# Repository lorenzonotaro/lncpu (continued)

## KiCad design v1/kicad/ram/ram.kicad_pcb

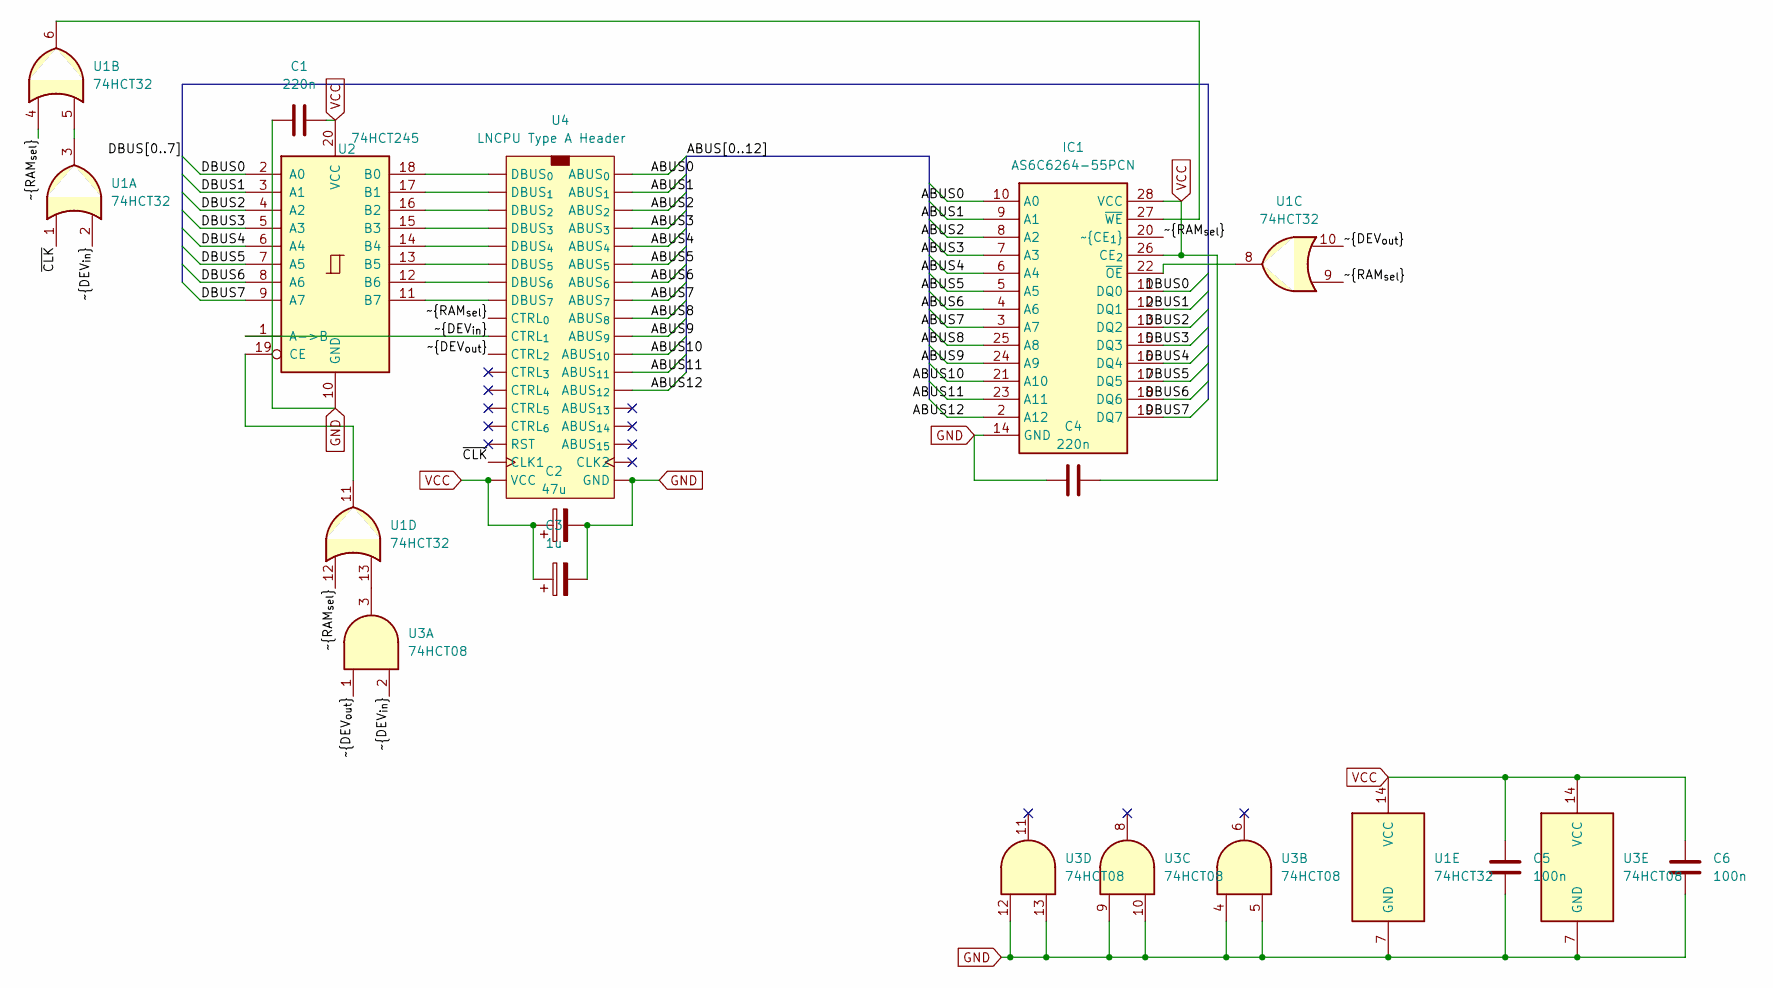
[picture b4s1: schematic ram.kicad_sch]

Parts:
C1, C4: 220n; C_Disc_D5.0mm_W2.5mm_P2.50mm
C2: 47u; CP_Radial_D5.0mm_P2.50mm
C3: 1u; CP_Radial_D4.0mm_P2.00mm-Large-Holes
C5, C6: 100n; C_Disc_D5.0mm_W2.5mm_P2.50mm
IC1: AS6C6264-55PCN; DIP1524W51P254L3632H394Q28N; Mouser Part Number 913-AS6C6264-55PCN
U1: 74HCT32; DIP-14_W7.62mm_LongPads
U2: 74HCT245; DIP-20_W7.62mm_LongPads
U3: 74HCT08; DIP-14_W7.62mm_LongPads
U4: LNCPU Type A Header; LNCPU_Type_A_Header

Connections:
/ABUS0: IC1.10 (A0), U4.4 (ABUS_{0})
/ABUS1: IC1.9 (A1), U4.6 (ABUS_{1})
/ABUS2: IC1.8 (A2), U4.8 (ABUS_{2})
/ABUS3: IC1.7 (A3), U4.10 (ABUS_{3})
/ABUS4: IC1.6 (A4), U4.12 (ABUS_{4})
/ABUS5: IC1.5 (A5), U4.14 (ABUS_{5})
/ABUS6: IC1.4 (A6), U4.16 (ABUS_{6})
/ABUS7: IC1.3 (A7), U4.18 (ABUS_{7})
/ABUS8: IC1.25 (A8), U4.20 (ABUS_{8})
/ABUS9: IC1.24 (A9), U4.22 (ABUS_{9})
/ABUS10: IC1.21 (A10), U4.24 (ABUS_{10})
/ABUS11: IC1.23 (A11), U4.26 (ABUS_{11})
/ABUS12: IC1.2 (A12), U4.28 (ABUS_{12})
/DBUS0: IC1.11 (DQ0), U2.2 (A0)
/DBUS1: IC1.12 (DQ1), U2.3 (A1)
/DBUS2: IC1.13 (DQ2), U2.4 (A2)
/DBUS3: IC1.15 (DQ3), U2.5 (A3)
/DBUS4: IC1.16 (DQ4), U2.6 (A4)
/DBUS5: IC1.17 (DQ5), U2.7 (A5)
/DBUS6: IC1.18 (DQ6), U2.8 (A6)
/DBUS7: IC1.19 (DQ7), U2.9 (A7)
/~CLK: U1.1, U4.35 (CLK1)
/~DEV_{in}: U1.2, U2.1 (A->B), U3.2, U4.5 (CTRL_{1})
/~DEV_{out}: U1.10, U3.1, U4.7 (CTRL_{2})
/~RAM_{sel}: IC1.20 (~CE_{1}), U1.4, U1.9, U1.12, U4.3 (CTRL_{0})
GND: C1.1, C2.2, C3.2, C4.1, C5.1, C6.1, IC1.14 (GND), U1.7 (GND), U2.10 (GND), U3.4, U3.5, U3.7 (GND), U3.9, U3.10, U3.12, U3.13, U4.1 (GND), U4.37 (GND), U4.38 (GND), U4.39 (GND)
unnamed: IC1.22 (~OE), U1.8
unnamed: IC1.27 (~WE), U1.6
unnamed: U1.3, U1.5
unnamed: U1.13, U3.3
unnamed: U2.18 (B0), U4.19 (DBUS_{0})
unnamed: U2.17 (B1), U4.21 (DBUS_{1})
unnamed: U2.16 (B2), U4.23 (DBUS_{2})
unnamed: U2.15 (B3), U4.25 (DBUS_{3})
unnamed: U2.14 (B4), U4.27 (DBUS_{4})
unnamed: U2.13 (B5), U4.29 (DBUS_{5})
unnamed: U2.12 (B6), U4.31 (DBUS_{6})
unnamed: U2.11 (B7), U4.33 (DBUS_{7})
unnamed: U1.11, U2.19 (CE)
VCC: C1.2, C2.1, C3.1, C4.2, C5.2, C6.2, IC1.26 (CE_{2}), IC1.28 (VCC), U1.14 (VCC), U2.20 (VCC), U3.14 (VCC), U4.2 (VCC), U4.40 (VCC)

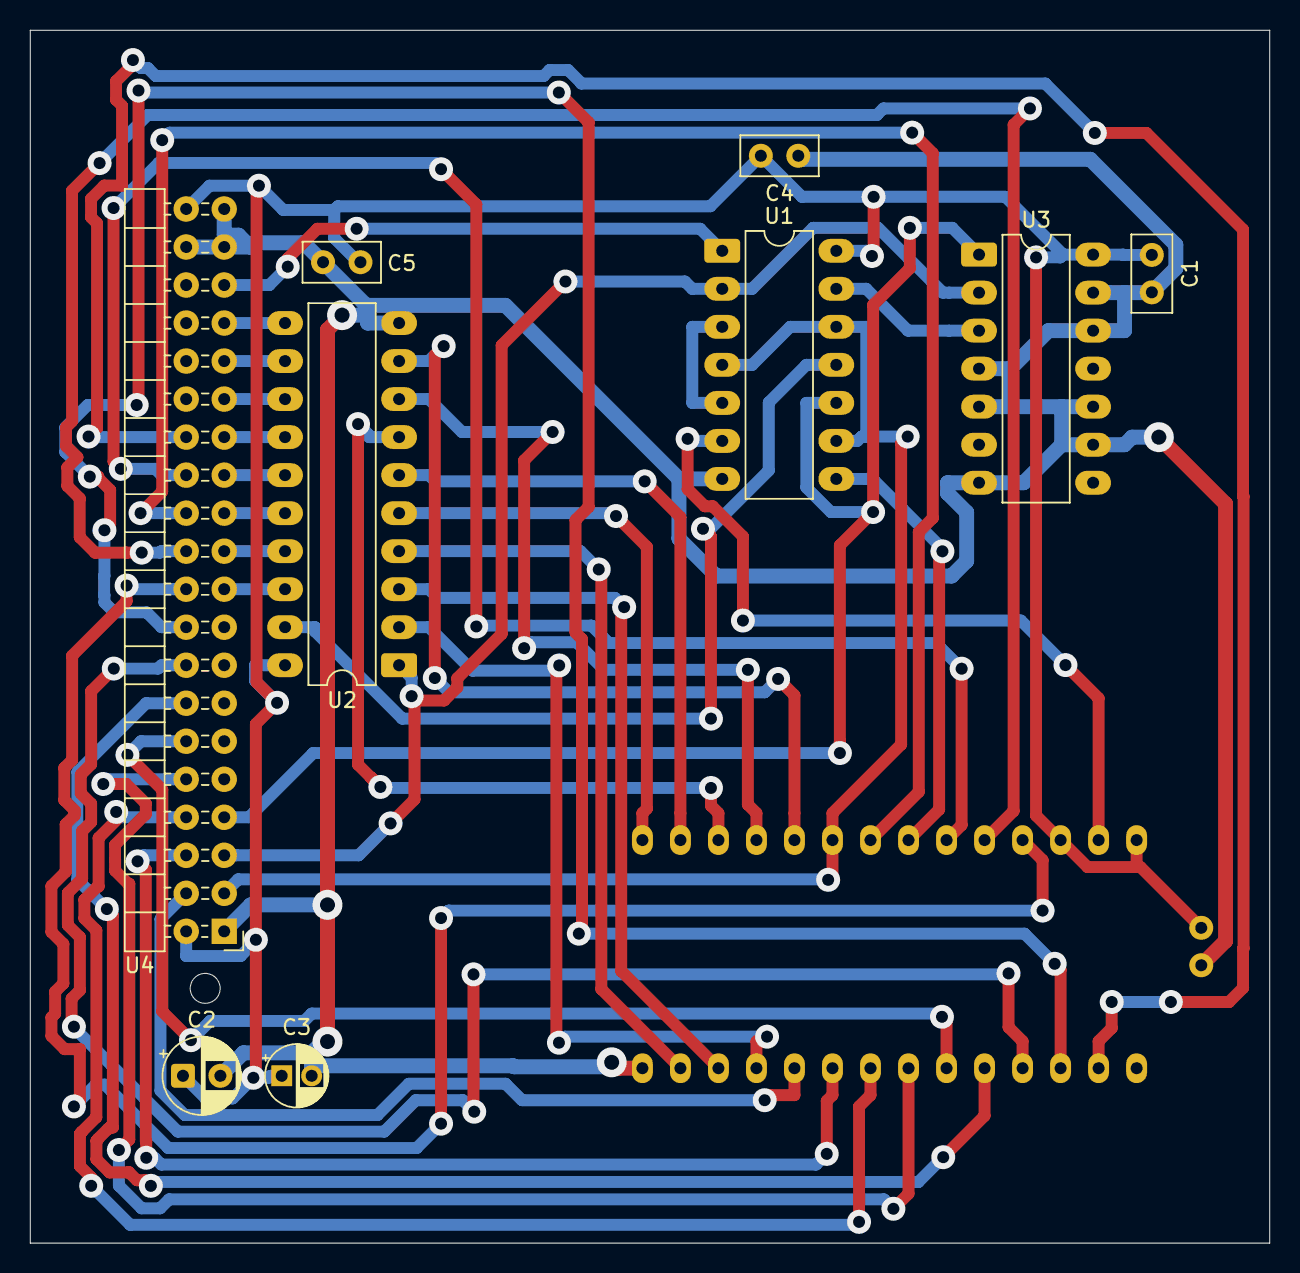
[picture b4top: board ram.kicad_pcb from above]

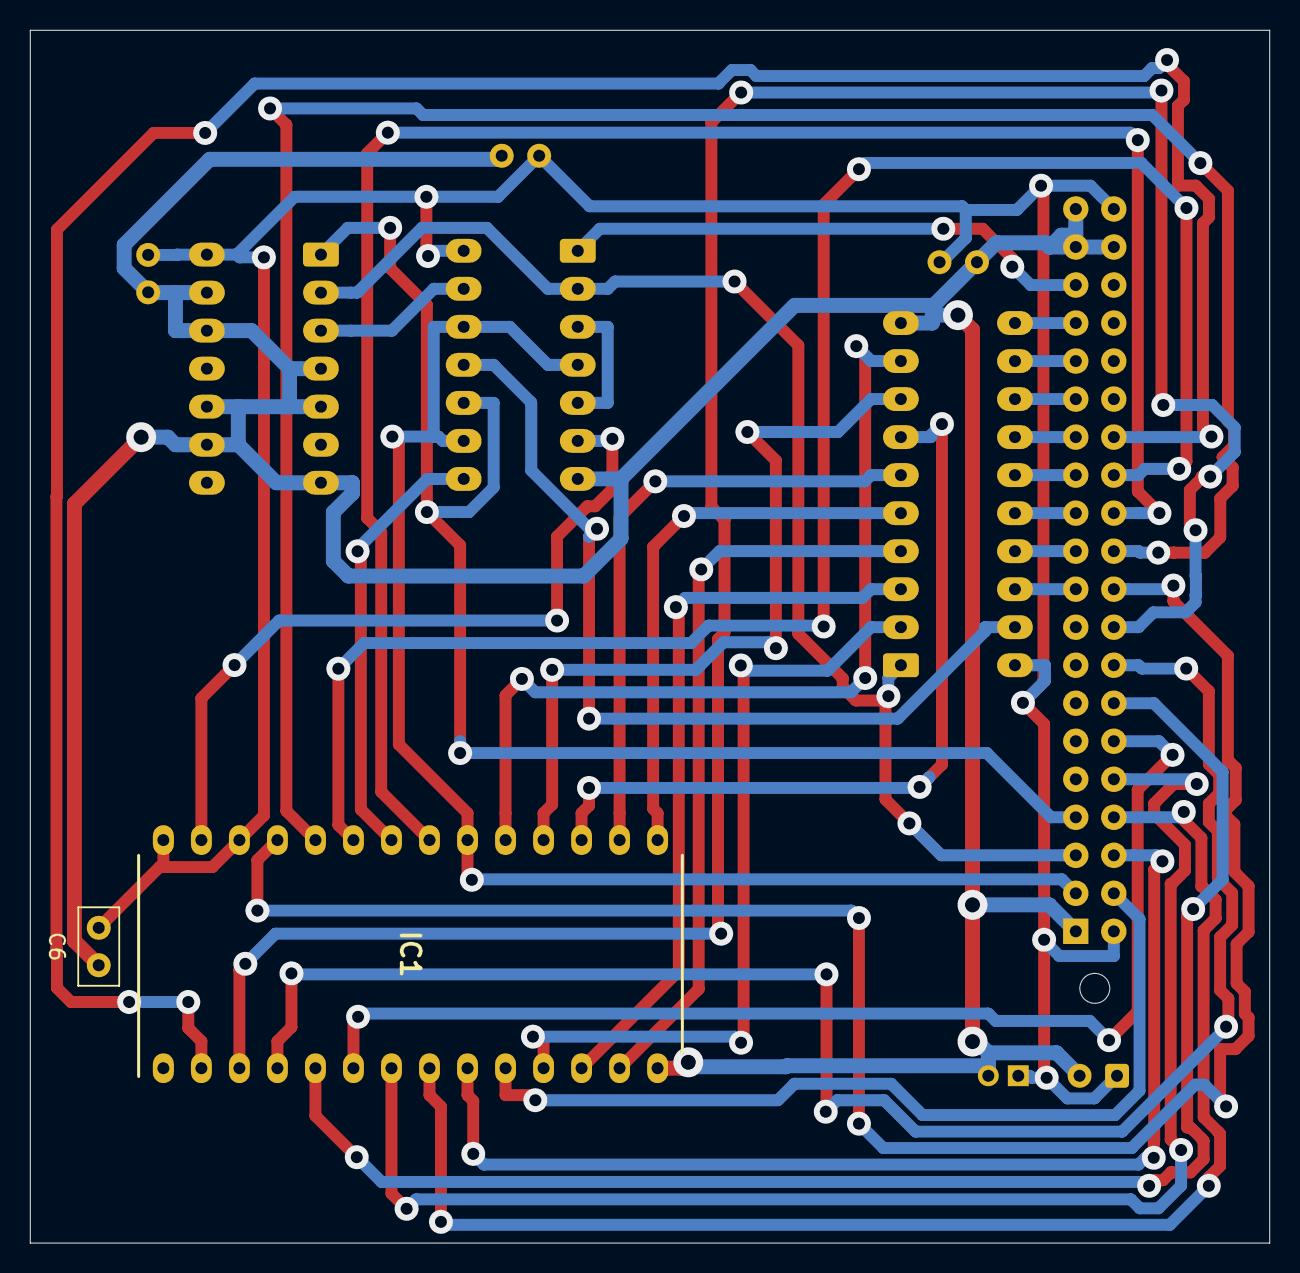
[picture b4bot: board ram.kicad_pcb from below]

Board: 2 copper layers, 82.8 x 81.0 mm, 11 parts (2 on the bottom side), 40 nets.

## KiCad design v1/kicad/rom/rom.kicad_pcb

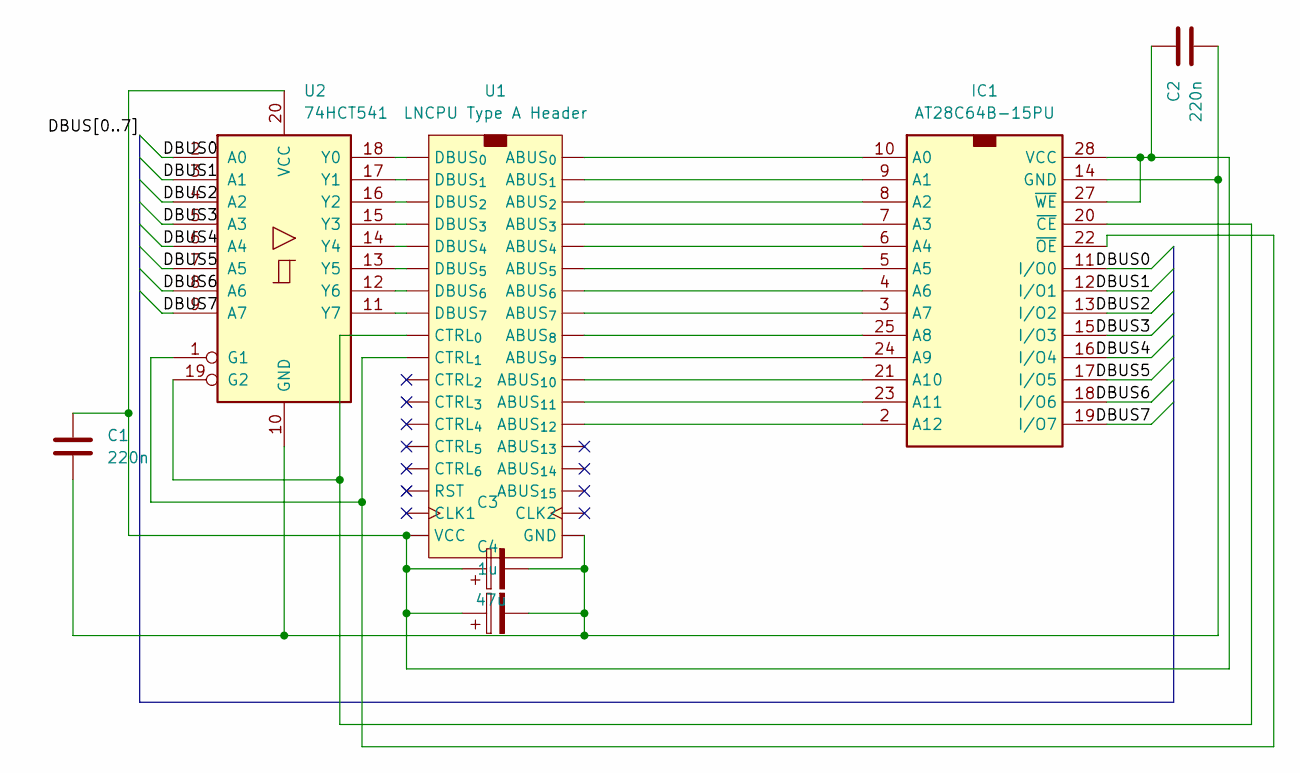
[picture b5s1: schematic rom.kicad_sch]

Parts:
C1, C2: 220n; C_Disc_D5.0mm_W2.5mm_P2.50mm
C3: 47u; CP_Radial_D5.0mm_P2.00mm
C4: 1u; CP_Radial_D4.0mm_P2.00mm-Large-Holes
IC1: AT28C64B-15PU; DIP1556W56P254L3702H483Q28N; Manufacturer_Part_Number AT28C64B-15PU; Mouser Part Number 556-AT28C64B15PU
U1: LNCPU Type A Header; LNCPU_Type_A_Header
U2: 74HCT541; DIP-20_W7.62mm_LongPads

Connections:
/DBUS0: IC1.11 (I/O0), U2.2 (A0)
/DBUS1: IC1.12 (I/O1), U2.3 (A1)
/DBUS2: IC1.13 (I/O2), U2.4 (A2)
/DBUS3: IC1.15 (I/O3), U2.5 (A3)
/DBUS4: IC1.16 (I/O4), U2.6 (A4)
/DBUS5: IC1.17 (I/O5), U2.7 (A5)
/DBUS6: IC1.18 (I/O6), U2.8 (A6)
/DBUS7: IC1.19 (I/O7), U2.9 (A7)
unnamed: IC1.10 (A0), U1.4 (ABUS_{0})
unnamed: IC1.9 (A1), U1.6 (ABUS_{1})
unnamed: IC1.8 (A2), U1.8 (ABUS_{2})
unnamed: IC1.7 (A3), U1.10 (ABUS_{3})
unnamed: IC1.6 (A4), U1.12 (ABUS_{4})
unnamed: IC1.5 (A5), U1.14 (ABUS_{5})
unnamed: IC1.4 (A6), U1.16 (ABUS_{6})
unnamed: IC1.3 (A7), U1.18 (ABUS_{7})
unnamed: IC1.25 (A8), U1.20 (ABUS_{8})
unnamed: IC1.24 (A9), U1.22 (ABUS_{9})
unnamed: IC1.21 (A10), U1.24 (ABUS_{10})
unnamed: IC1.23 (A11), U1.26 (ABUS_{11})
unnamed: IC1.2 (A12), U1.28 (ABUS_{12})
unnamed: C1.2, C2.2, C3.2, C4.2, IC1.14 (GND), U1.1 (GND), U1.37 (GND), U1.38 (GND), U1.39 (GND), U2.10 (GND)
unnamed: C1.1, C2.1, C3.1, C4.1, IC1.27 (~WE), IC1.28 (VCC), U1.2 (VCC), U1.40 (VCC), U2.20 (VCC)
unnamed: IC1.20 (~CE), U1.3 (CTRL_{0}), U2.19 (G2)
unnamed: IC1.22 (~OE), U1.5 (CTRL_{1}), U2.1 (G1)
unnamed: U1.19 (DBUS_{0}), U2.18 (Y0)
unnamed: U1.21 (DBUS_{1}), U2.17 (Y1)
unnamed: U1.23 (DBUS_{2}), U2.16 (Y2)
unnamed: U1.25 (DBUS_{3}), U2.15 (Y3)
unnamed: U1.27 (DBUS_{4}), U2.14 (Y4)
unnamed: U1.29 (DBUS_{5}), U2.13 (Y5)
unnamed: U1.31 (DBUS_{6}), U2.12 (Y6)
unnamed: U1.33 (DBUS_{7}), U2.11 (Y7)

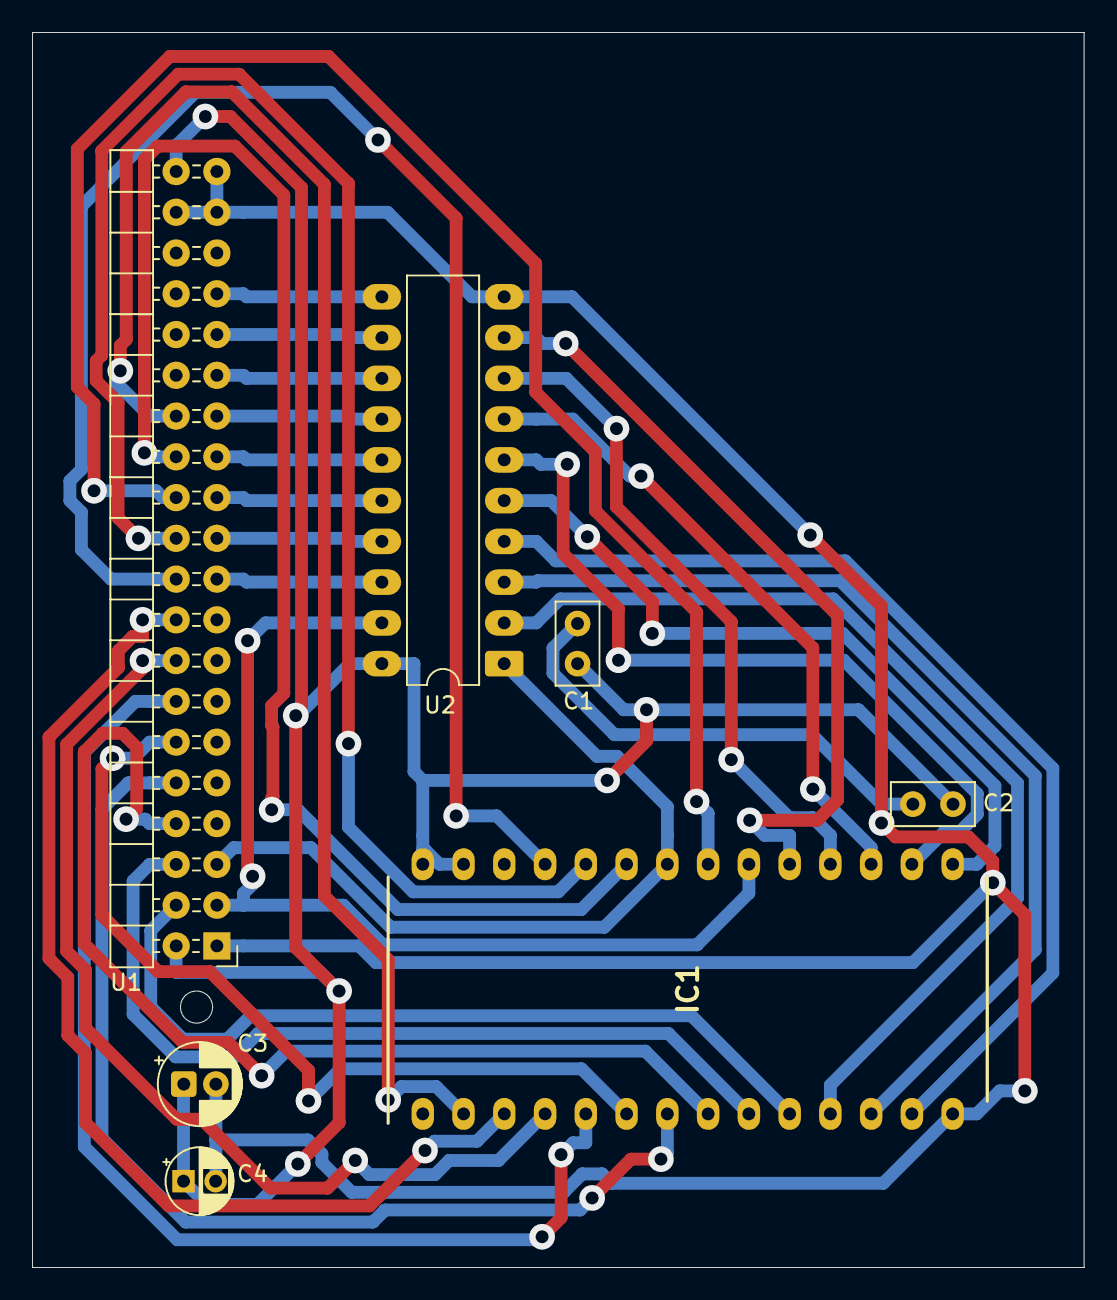
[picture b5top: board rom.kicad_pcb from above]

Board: 2 copper layers, 65.5 x 77.0 mm, 7 parts (0 on the bottom side), 33 nets.

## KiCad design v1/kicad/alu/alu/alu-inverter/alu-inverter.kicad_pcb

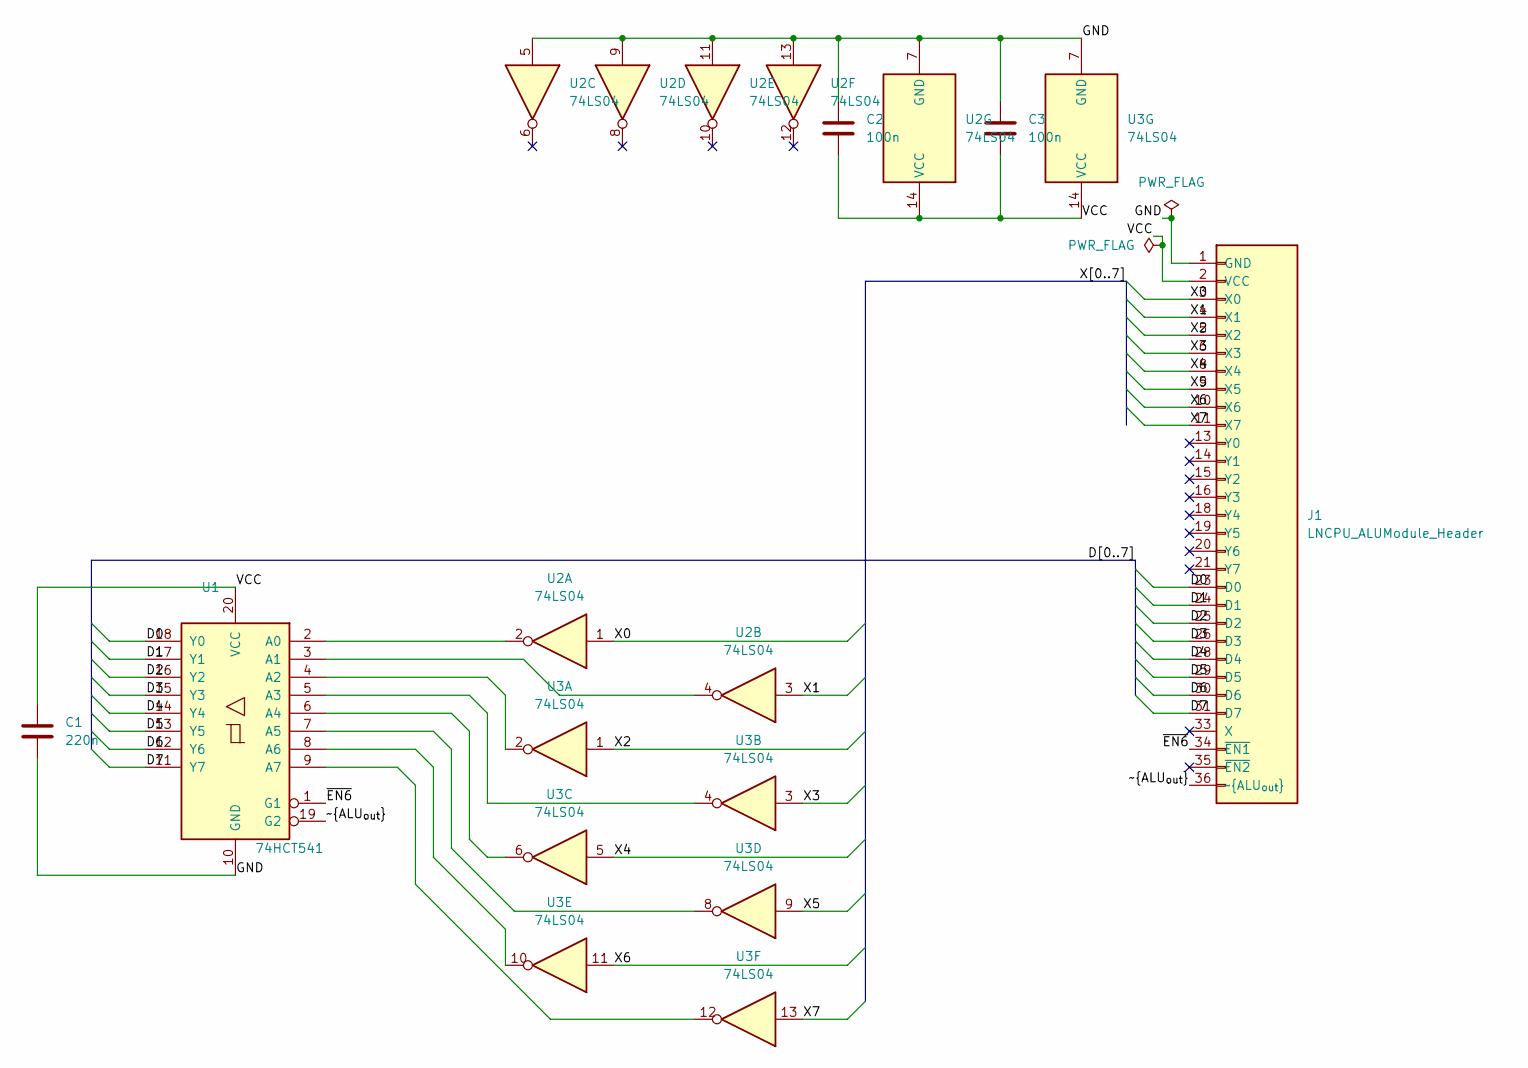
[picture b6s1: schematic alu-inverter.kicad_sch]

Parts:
C1: 220n; C_Disc_D5.0mm_W2.5mm_P5.00mm
C2, C3: 100n; C_Disc_D5.0mm_W2.5mm_P5.00mm
J1: LNCPU_ALUModule_Header; LNCPU_ALU_Module_Header
U1: 74HCT541; DIP-20_W7.62mm_LongPads
U2, U3: 74LS04; DIP-14_W7.62mm_LongPads

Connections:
/D0: J1.23 (D0), U1.18 (Y0)
/D1: J1.24 (D1), U1.17 (Y1)
/D2: J1.25 (D2), U1.16 (Y2)
/D3: J1.26 (D3), U1.15 (Y3)
/D4: J1.28 (D4), U1.14 (Y4)
/D5: J1.29 (D5), U1.13 (Y5)
/D6: J1.30 (D6), U1.12 (Y6)
/D7: J1.31 (D7), U1.11 (Y7)
/GND: C1.2, C2.1, C3.1, J1.1 (GND), J1.7 (GND), J1.12 (GND), J1.17 (GND), J1.22 (GND), J1.27 (GND), J1.32 (GND), J1.37 (GND), U1.10 (GND), U2.5, U2.7 (GND), U2.9, U2.11, U2.13, U3.7 (GND)
/VCC: C1.1, C2.2, C3.2, J1.2 (VCC), J1.38 (VCC), U1.20 (VCC), U2.14 (VCC), U3.14 (VCC)
/X0: J1.3 (X0), U2.1
/X1: J1.4 (X1), U2.3
/X2: J1.5 (X2), U3.1
/X3: J1.6 (X3), U3.3
/X4: J1.8 (X4), U3.5
/X5: J1.9 (X5), U3.9
/X6: J1.10 (X6), U3.11
/X7: J1.11 (X7), U3.13
/~ALU_{out}: J1.36 (~ALU_{out}), U1.19 (G2)
/~EN6: J1.34 (~EN1), U1.1 (G1)
unnamed: U1.2 (A0), U2.2
unnamed: U1.3 (A1), U2.4
unnamed: U1.4 (A2), U3.2
unnamed: U1.5 (A3), U3.4
unnamed: U1.6 (A4), U3.6
unnamed: U1.7 (A5), U3.8
unnamed: U1.8 (A6), U3.10
unnamed: U1.9 (A7), U3.12

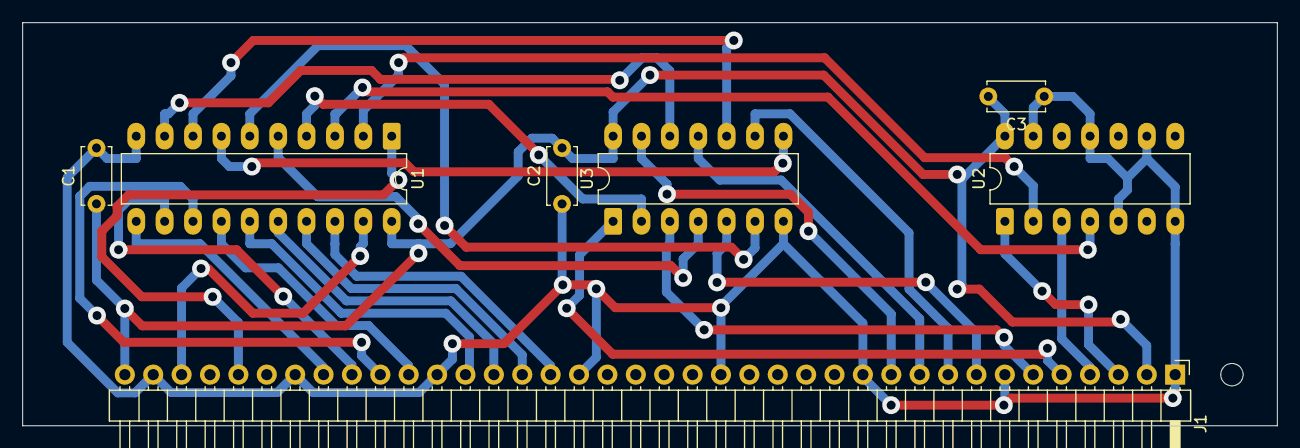
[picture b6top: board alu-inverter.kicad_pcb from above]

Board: 2 copper layers, 112.3 x 36.1 mm, 7 parts (0 on the bottom side), 28 nets.

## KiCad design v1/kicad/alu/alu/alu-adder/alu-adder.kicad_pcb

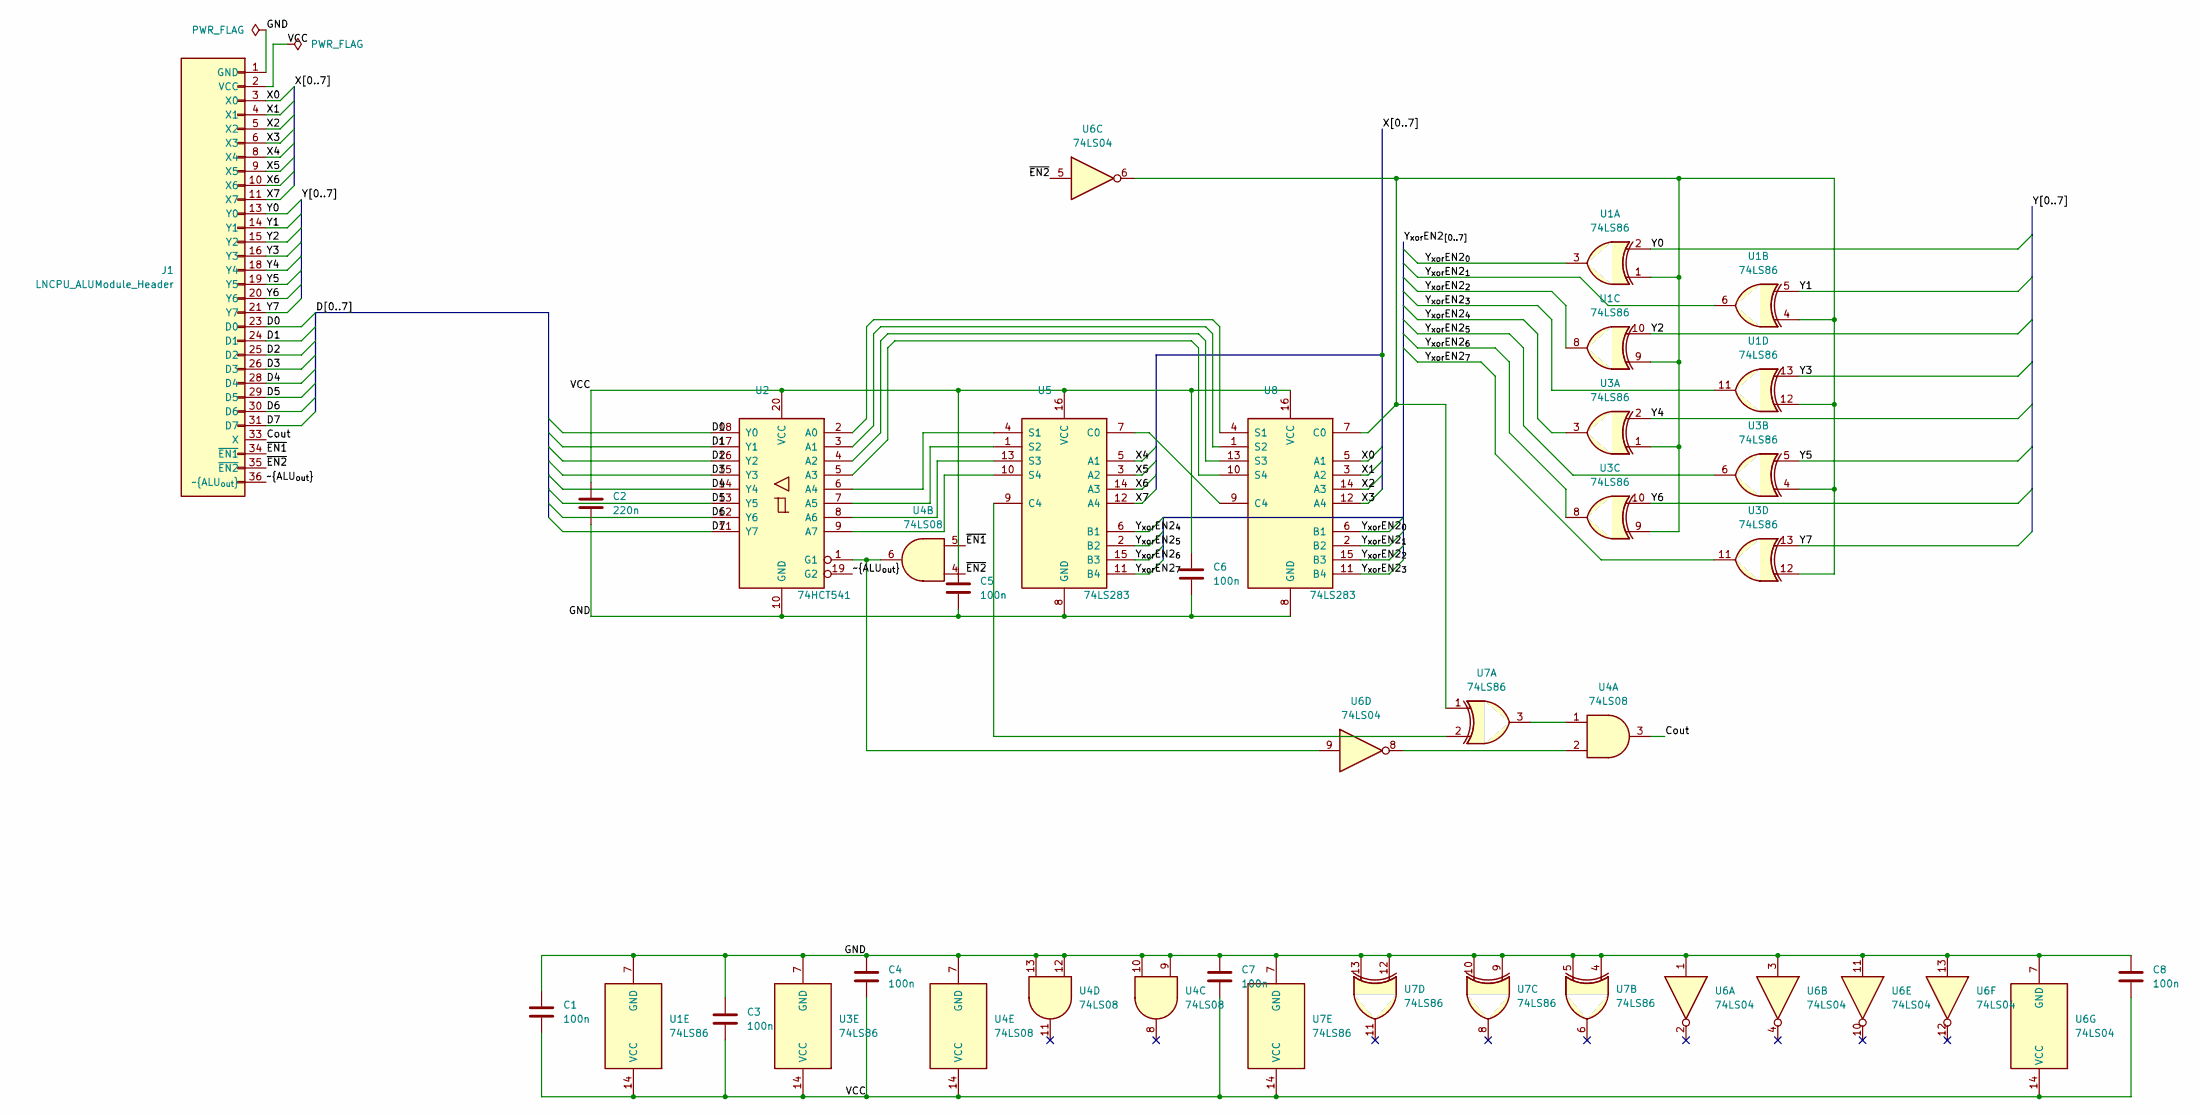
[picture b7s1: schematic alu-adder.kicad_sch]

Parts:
C1, C3, C4, C5, C6, C7, C8: 100n; C_Disc_D5.0mm_W2.5mm_P5.00mm
C2: 220n; C_Disc_D5.0mm_W2.5mm_P5.00mm
J1: LNCPU_ALUModule_Header; LNCPU_ALU_Module_Header
U1, U3, U7: 74LS86; DIP-14_W7.62mm_LongPads
U2: 74HCT541; DIP-20_W7.62mm_LongPads
U4: 74LS08; DIP-14_W7.62mm_LongPads
U5, U8: 74LS283; DIP-16_W7.62mm_LongPads
U6: 74LS04; DIP-14_W7.62mm_LongPads

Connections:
/Cout: J1.33 (X), U4.3
/D0: J1.23 (D0), U2.18 (Y0)
/D1: J1.24 (D1), U2.17 (Y1)
/D2: J1.25 (D2), U2.16 (Y2)
/D3: J1.26 (D3), U2.15 (Y3)
/D4: J1.28 (D4), U2.14 (Y4)
/D5: J1.29 (D5), U2.13 (Y5)
/D6: J1.30 (D6), U2.12 (Y6)
/D7: J1.31 (D7), U2.11 (Y7)
/GND: C1.1, C2.2, C3.1, C4.1, C5.2, C6.2, C7.1, C8.1, J1.1 (GND), J1.7 (GND), J1.12 (GND), J1.17 (GND), J1.22 (GND), J1.27 (GND), J1.32 (GND), J1.37 (GND), U1.7 (GND), U2.10 (GND), U3.7 (GND), U4.7 (GND), U4.9, U4.10, U4.12, U4.13, U5.8 (GND), U6.1, U6.3, U6.7 (GND), U6.11, U6.13, U7.4, U7.5, U7.7 (GND), U7.9, U7.10, U7.12, U7.13, U8.8 (GND)
/VCC: C1.2, C2.1, C3.2, C4.2, C5.1, C6.1, C7.2, C8.2, J1.2 (VCC), J1.38 (VCC), U1.14 (VCC), U2.20 (VCC), U3.14 (VCC), U4.14 (VCC), U5.16 (VCC), U6.14 (VCC), U7.14 (VCC), U8.16 (VCC)
/X0: J1.3 (X0), U8.5 (A1)
/X1: J1.4 (X1), U8.3 (A2)
/X2: J1.5 (X2), U8.14 (A3)
/X3: J1.6 (X3), U8.12 (A4)
/X4: J1.8 (X4), U5.5 (A1)
/X5: J1.9 (X5), U5.3 (A2)
/X6: J1.10 (X6), U5.14 (A3)
/X7: J1.11 (X7), U5.12 (A4)
/Y0: J1.13 (Y0), U1.2
/Y1: J1.14 (Y1), U1.5
/Y2: J1.15 (Y2), U1.10
/Y3: J1.16 (Y3), U1.13
/Y4: J1.18 (Y4), U3.2
/Y5: J1.19 (Y5), U3.5
/Y6: J1.20 (Y6), U3.10
/Y7: J1.21 (Y7), U3.13
/Y_{xor}EN2_{0}: U1.3, U8.6 (B1)
/Y_{xor}EN2_{1}: U1.6, U8.2 (B2)
/Y_{xor}EN2_{2}: U1.8, U8.15 (B3)
/Y_{xor}EN2_{3}: U1.11, U8.11 (B4)
/Y_{xor}EN2_{4}: U3.3, U5.6 (B1)
/Y_{xor}EN2_{5}: U3.6, U5.2 (B2)
/Y_{xor}EN2_{6}: U3.8, U5.15 (B3)
/Y_{xor}EN2_{7}: U3.11, U5.11 (B4)
/~ALU_{out}: J1.36 (~ALU_{out}), U2.19 (G2)
/~EN1: J1.34 (~EN1), U4.5
/~EN2: J1.35 (~EN2), U4.4, U6.5
unnamed: U2.2 (A0), U8.4 (S1)
unnamed: U2.3 (A1), U8.1 (S2)
unnamed: U2.4 (A2), U8.13 (S3)
unnamed: U2.5 (A3), U8.10 (S4)
unnamed: U2.6 (A4), U5.4 (S1)
unnamed: U2.7 (A5), U5.1 (S2)
unnamed: U2.8 (A6), U5.13 (S3)
unnamed: U2.9 (A7), U5.10 (S4)
unnamed: U2.1 (G1), U4.6, U6.9
unnamed: U4.1, U7.3
unnamed: U4.2, U6.8
unnamed: U5.7 (C0), U8.9 (C4)
unnamed: U5.9 (C4), U7.2
unnamed: U1.1, U1.4, U1.9, U1.12, U3.1, U3.4, U3.9, U3.12, U6.6, U7.1, U8.7 (C0)

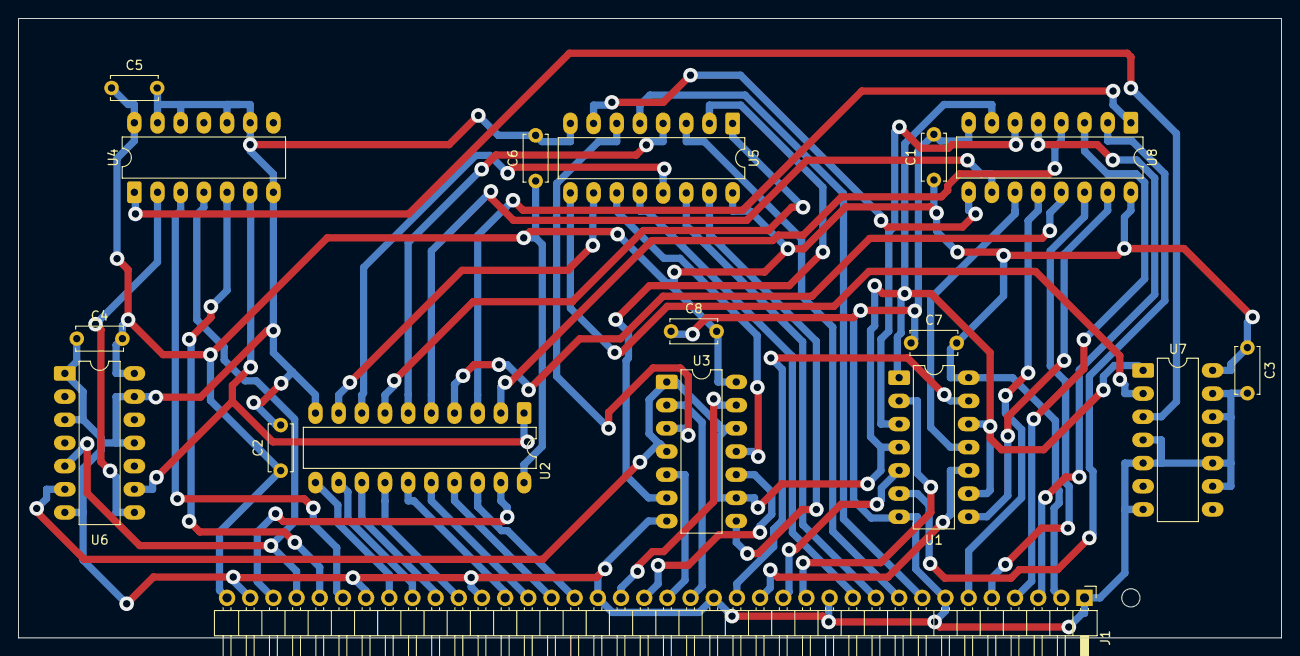
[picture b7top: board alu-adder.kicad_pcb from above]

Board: 2 copper layers, 138.4 x 67.9 mm, 17 parts (0 on the bottom side), 52 nets.

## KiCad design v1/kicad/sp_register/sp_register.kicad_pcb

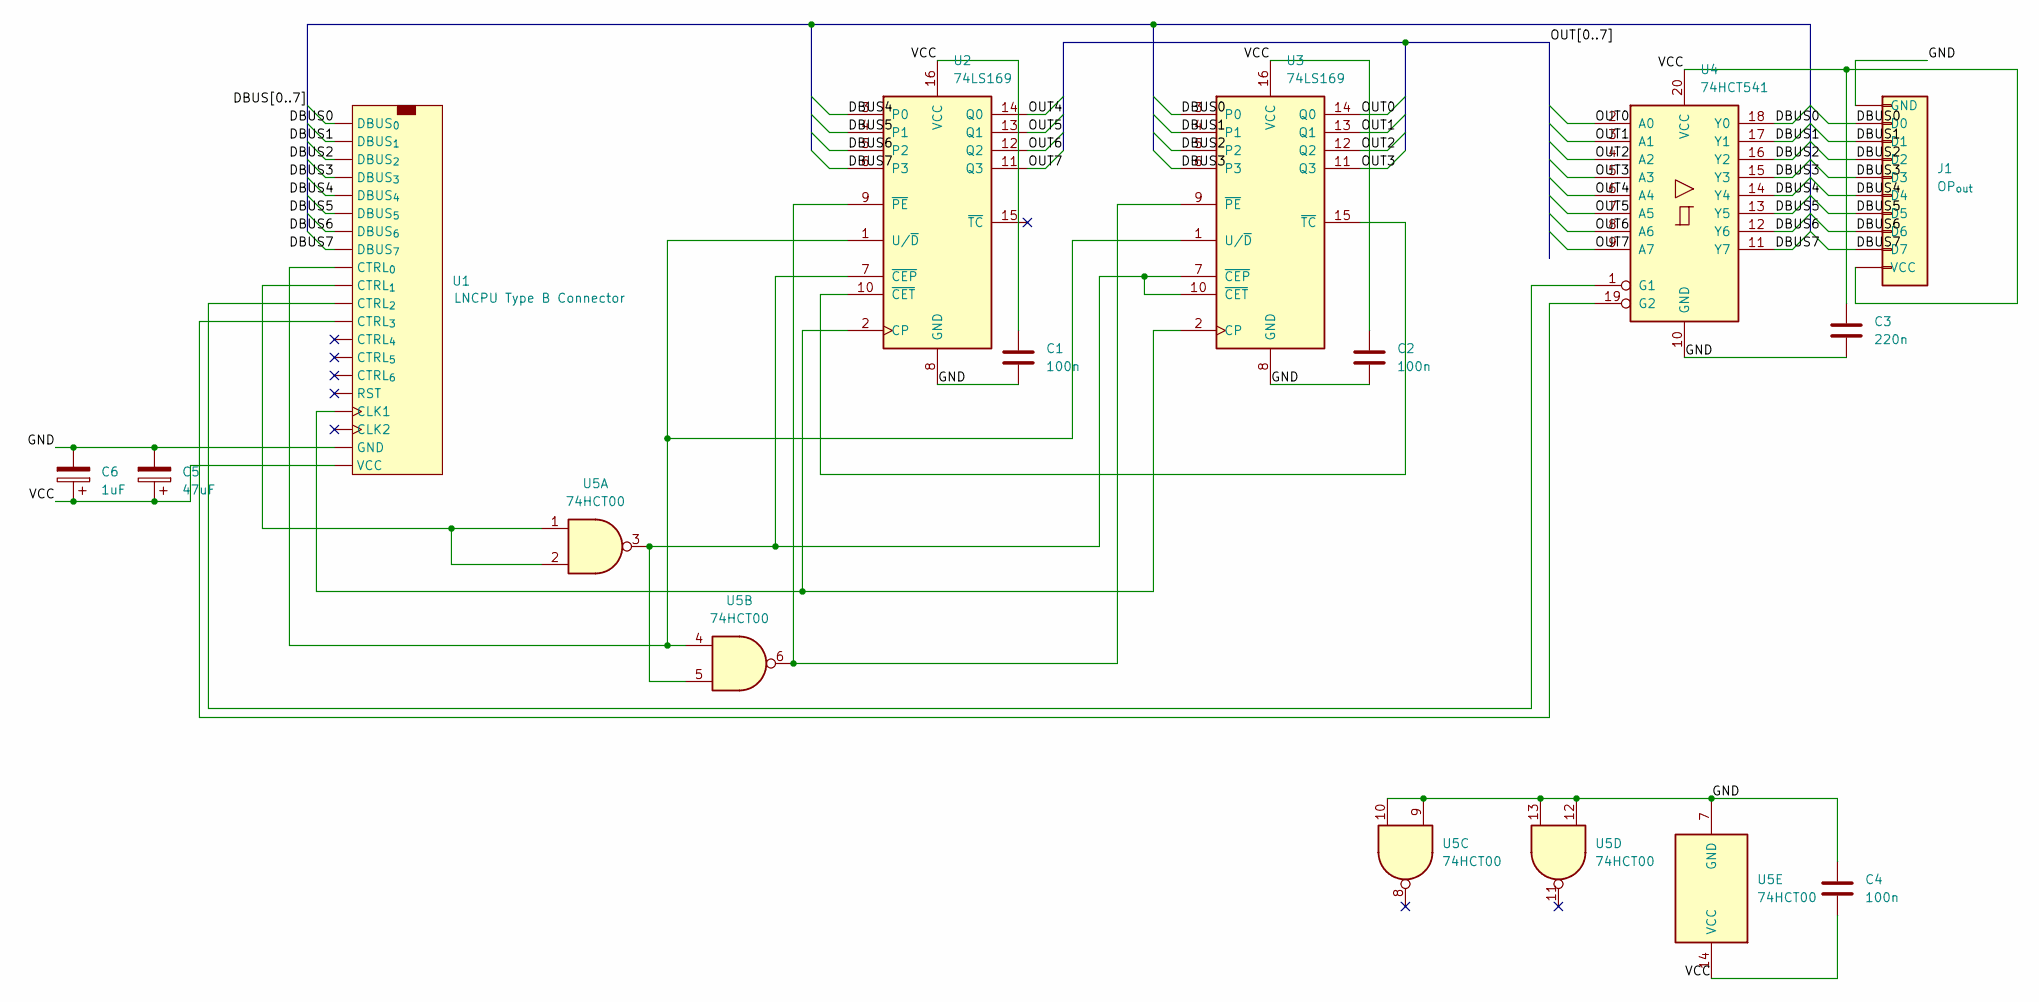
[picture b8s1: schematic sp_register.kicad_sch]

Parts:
C1, C2, C4: 100n; C_Disc_D5.0mm_W2.5mm_P5.00mm
C3: 220n; C_Disc_D5.0mm_W2.5mm_P5.00mm
C5: 47uF; CP_Radial_D5.0mm_P2.00mm
C6: 1uF; CP_Radial_D4.0mm_P2.00mm-Large-Holes
J1: OP_{out}; PinSocket_1x10_P2.54mm_Vertical
U1: LNCPU Type B Connector; LNCPU_Type_B_Header
U2, U3: 74LS169; DIP-16_W7.62mm_LongPads
U4: 74HCT541; DIP-20_W7.62mm_LongPads
U5: 74HCT00; DIP-14_W7.62mm

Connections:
/DBUS0: J1.2 (D0), U1.4 (DBUS_{0}), U3.3 (P0), U4.18 (Y0)
/DBUS1: J1.3 (D1), U1.6 (DBUS_{1}), U3.4 (P1), U4.17 (Y1)
/DBUS2: J1.4 (D2), U1.8 (DBUS_{2}), U3.5 (P2), U4.16 (Y2)
/DBUS3: J1.5 (D3), U1.10 (DBUS_{3}), U3.6 (P3), U4.15 (Y3)
/DBUS4: J1.6 (D4), U1.12 (DBUS_{4}), U2.3 (P0), U4.14 (Y4)
/DBUS5: J1.7 (D5), U1.14 (DBUS_{5}), U2.4 (P1), U4.13 (Y5)
/DBUS6: J1.8 (D6), U1.16 (DBUS_{6}), U2.5 (P2), U4.12 (Y6)
/DBUS7: J1.9 (D7), U1.18 (DBUS_{7}), U2.6 (P3), U4.11 (Y7)
/GND: C1.2, C2.2, C3.2, C4.1, C5.2, C6.2, J1.1 (GND), U1.1 (GND), U1.17 (GND), U1.20 (GND), U1.22 (GND), U2.8 (GND), U3.8 (GND), U4.10 (GND), U5.7 (GND), U5.9, U5.10, U5.12, U5.13
/OUT0: U3.14 (Q0), U4.2 (A0)
/OUT1: U3.13 (Q1), U4.3 (A1)
/OUT2: U3.12 (Q2), U4.4 (A2)
/OUT3: U3.11 (Q3), U4.5 (A3)
/OUT4: U2.14 (Q0), U4.6 (A4)
/OUT5: U2.13 (Q1), U4.7 (A5)
/OUT6: U2.12 (Q2), U4.8 (A6)
/OUT7: U2.11 (Q3), U4.9 (A7)
/VCC: C1.1, C2.1, C3.1, C4.2, C5.1, C6.1, J1.10 (VCC), U1.2 (VCC), U1.24 (VCC), U2.16 (VCC), U3.16 (VCC), U4.20 (VCC), U5.14 (VCC)
unnamed: U1.21 (CLK1), U2.2 (CP), U3.2 (CP)
unnamed: U1.3 (CTRL_{0}), U2.1 (U/~D), U3.1 (U/~D), U5.4
unnamed: U1.5 (CTRL_{1}), U5.1, U5.2
unnamed: U1.7 (CTRL_{2}), U4.1 (G1)
unnamed: U1.9 (CTRL_{3}), U4.19 (G2)
unnamed: U2.7 (~CEP), U3.7 (~CEP), U3.10 (~CET), U5.3, U5.5
unnamed: U2.10 (~CET), U3.15 (~TC)
unnamed: U2.9 (~PE), U3.9 (~PE), U5.6

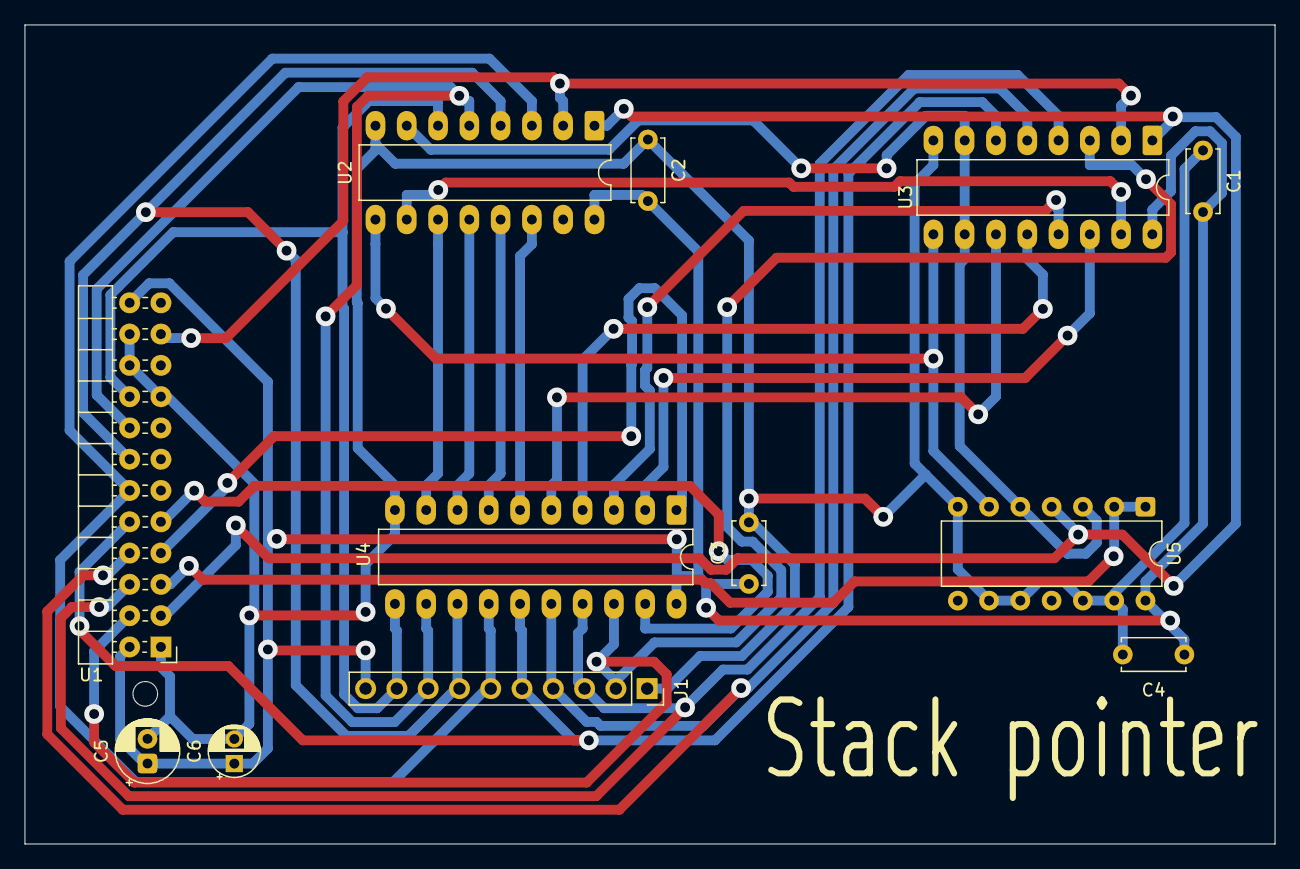
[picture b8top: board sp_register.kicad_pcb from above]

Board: 2 copper layers, 101.5 x 66.5 mm, 12 parts (0 on the bottom side), 26 nets.
